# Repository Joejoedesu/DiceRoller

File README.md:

It is a Dice Roller Blessed by Nahida!
Wish you all the wisdom and fortune.

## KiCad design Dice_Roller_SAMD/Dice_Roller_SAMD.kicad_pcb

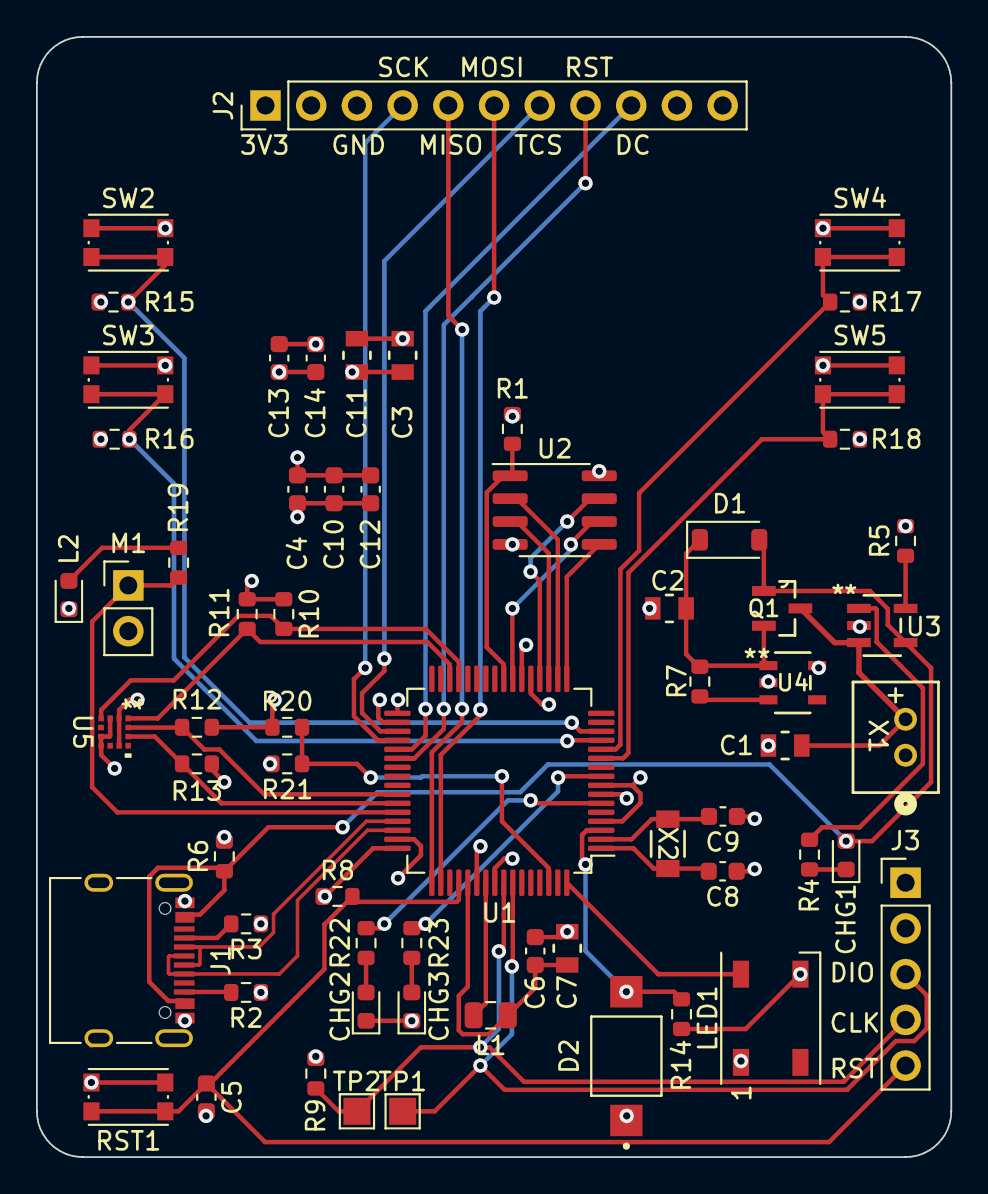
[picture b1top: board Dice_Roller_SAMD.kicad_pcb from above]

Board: 4 copper layers, 50.8 x 62.2 mm, 64 parts (0 on the bottom side), 49 nets.

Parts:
C1, C2, C3, C7, C11: 10uF; G-21_MUR
C4, C5, C6, C10, C12, C13: 1uF; C_0603_1608Metric
C8, C9: 22pF; C_0603_1608Metric
C14: 0.1uF; C_0603_1608Metric
CHG1, CHG3: ORANGE; LED_0603_1608Metric
CHG2: RED; LED_0603_1608Metric
D1: MBR054; D_SOD-123
D2: QSB34CGR; XDCR_QSB34CGR
J1: USB_C_Receptacle_USB2.0; USB_C_Receptacle_XKB_U262-16XN-4BVC11
J2: Conn_01x11; PinHeader_1x11_P2.54mm_Vertical
J3: Conn_01x05; PinHeader_1x05_P2.54mm_Vertical
L1: 10uH; C_0805_2012Metric
L2: RED; LED_0603_1608Metric
LED1: LED_WS2812B_PLCC4_5.0x5.0mm_P3.2mm
M1: Motor_DC; PinHeader_1x02_P2.54mm_Vertical
Q1: DMG3415; SOT95P240X105-3N
R1, R7, R8, R9, R15, R16, R17, R18, R22, R23: 10K; R_0603_1608Metric
R2, R3, R5: 5.1K; R_0603_1608Metric
R4: 1K; R_0603_1608Metric
R6, R20, R21: 100K; R_0603_1608Metric
R10, R11, R12, R13, R14: 4.7K; R_0603_1608Metric
R19: 2.2K; R_0603_1608Metric
RST1: SW_Push_1P1T_NO_CK_KMR2
SW2, SW3, SW4, SW5: SW_Push_1P1T_NO_CK_KMR2
TP1, TP2: TESTPOINTROUND1.5MM; TestPoint_Pad_1.5x1.5mm
U1: ATSAMD51J20A-A; TQFP-64_10x10mm_P0.5mm
U2: 25Q16; SOIC-8_3.9x4.9mm_P1.27mm
U3: MCP73831T-2ACI/OT; SOT-23-5_MC_MCH
U4: AP2112-3.3; SOT_RG1_DIO
U5: MC3479; MC3479_MEM
X1: JSTPH; CONN2_B2B-PH-K-S_JST
X2: 32.768; XTAL_ECS-31B_ECS

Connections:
+3V3: C3.1, C4.1, C10.1, C11.1, C12.1, C13.1, C14.1, D2.C, J2.1, J3.1, LED1.1 (VDD), R1.1, R8.1, R9.1, R10.1, R11.1, R12.1, R13.1, R20.1, SW2.1, SW3.1, SW4.1, SW5.1, U1.4 (PA03), U1.8 (VDDANA), U1.21 (VDDIOB), U1.34 (VDDIO), U1.48 (VDDIO), U1.56 (VDDIO), U2.8 (VCC), U4.5 (OUT), U5.2 (CSN), U5.9 (VDD)
/Module/DC: J2.9, U1.37 (PA18)
/Module/INTN1: R12.2, U1.42 (PA21), U5.12 (INTN_1)
/Module/INTN2: R13.2, U1.43 (PA22), U5.11 (INTN_2)
/Module/LED1: R22.2, U1.6 (PB05)
/Module/LED2: R23.2, U1.9 (PB06)
/Module/MISO: J2.5, U1.49 (PB22)
/Module/MOSI: J2.6, U1.50 (PB23)
/Module/Pht: D2.A, R14.1, U1.3 (PA02)
/Module/RST: J2.8, U1.38 (PA19)
/Module/S1: R15.1, SW2.2 (S), U1.14 (PA05)
/Module/S2: R16.1, SW3.2 (S), U1.13 (PA04)
/Module/S3: R17.1, SW4.2 (S), U1.12 (PB09)
/Module/S4: R18.1, SW5.2 (S), U1.11 (PB08)
/Module/SCK: J2.4, U1.36 (PA17)
/Module/SCL: R11.2, U1.30 (PA13), U5.1 (SCK_SCL)
/Module/SDA: R10.2, U1.29 (PA12), U5.4 (DIN_SDA)
/Module/TCS: J2.7, U1.35 (PA16)
/Module/Vib: M1.1 (+), R19.1, U1.44 (PA23)
/SAMD_51/D8_NEOPIX: LED1.4 (DI), U1.64 (PB03)
/SAMD_51/D+: J1.A6 (D+), J1.B6 (D+), U1.46 (PA25)
/SAMD_51/D-: J1.A7 (D-), J1.B7 (D-), U1.45 (PA24)
/SAMD_51/EN: R7.2, U4.3 (EN)
/SAMD_51/FLASH_CS: R1.2, U1.24 (PB11), U2.1 (SSEL)
/SAMD_51/FLASH_D0: U1.17 (PA08), U2.5 (MOSI)
/SAMD_51/FLASH_D1: U1.18 (PA09), U2.2 (MISO)
/SAMD_51/FLASH_D2: U1.19 (PA10), U2.3 (WP#/IO2)
/SAMD_51/FLASH_D3: U1.20 (PA11), U2.7 (HOLD#/IO3)
/SAMD_51/FLASH_SCK: U1.23 (PB10), U2.6 (SCK)
/SAMD_51/SWCLK: J3.4, R9.2, TP2.1, U1.57 (PA30)
/SAMD_51/SWDIO: J3.3, TP1.1, U1.58 (PA31)
/SAMD_51/V_DIV: R20.2, R21.1, U1.62 (PB01)
/SAMD_51/~RESET: C5.1, J3.5, R8.2, RST1.1, U1.52 (~RESET)
GND: C1.2, C2.2, C3.2, C4.2, C5.2, C6.2, C7.2, C8.1, C9.1, C10.2, C11.2, C12.2, C13.2, C14.2, CHG2.1 (C), CHG3.1 (C), J1.A1 (GND), J1.A12 (GND), J1.B1 (GND), J1.B12 (GND), J1.S1 (SHIELD), J2.3, J3.2, L2.1 (C), LED1.3 (GND), M1.2 (-), R2.1, R3.1, R5.2, R6.2, R14.2, R15.2, R16.2, R17.2, R18.2, R21.2, RST1.2 (S1), U1.7 (GNDANA), U1.22 (GND), U1.33 (GND), U1.47 (GND), U1.54 (GND), U2.4 (VSS), U3.2 (VSS), U4.2 (GND), U5.3 (DOUT_A6), U5.6 (GND), U5.7 (VPP), X1.1
unnamed: CHG1.1 (C), R4.1
unnamed: CHG2.2 (A), R22.1
unnamed: CHG3.2 (A), R23.1
unnamed: C2.1, D1.1 (C), Q1.2 (S), R7.1, U4.1 (IN)
unnamed: J1.A5 (CC1), R3.2
unnamed: J1.B5 (CC2), R2.2
unnamed: L2.2 (A), R19.2
unnamed: C8.2, U1.1 (PA00), X2.2
unnamed: C9.2, U1.2 (PA01), X2.1
unnamed: C6.1, C7.1, L1.1, U1.53 (VDDCORE)
unnamed: L1.2, U1.55 (VSW)
unnamed: R5.1, U3.5 (PROG)
unnamed: R4.2, U3.1 (STAT)
VBAT: C1.1, Q1.3 (D), U3.3 (VBAT), X1.2
VBUS: CHG1.2 (A), D1.2 (A), J1.A4 (VBUS), J1.A9 (VBUS), J1.B4 (VBUS), J1.B9 (VBUS), Q1.1 (G), R6.1, U3.4 (VDD)
